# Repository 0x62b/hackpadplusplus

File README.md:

# Hackpad++
6-key hot-swappable RGB backlit macropad based on Seeed Studio Xiao NRF52840. Uses ZMK for firmware.
400mAh battery, supports wireless BLE HID operation. I made this to use up some spare parts and learn more about ZMK.

Rn the firmware is in a really really really stripped down state because I want to get the physical thing before trying to make more firmware since it keeps breaking the build

According to ZMK's [power profiler](https://zmk.dev/power-profiler) we should get about 21 hours of battery life with the RGB at 20% brightness

## Repo Structure
CAD files in `cad/`\
KiCad design files in `PCB/`\
Production gerbers in `PCB/gerbers`\
Firmware in `firmware/`\
BOM at `bom.csv`\
Case Onshape design [here](https://cad.onshape.com/documents/916857c7e80611f775a72b60/w/b9c69dbfc296334dd1ffd629/e/9b910e13e67ad3b8cb3a877d?renderMode=0&uiState=69eb64186156e8d7dafdc7be)

## 3D Models
https://grabcad.com/library/oled-0-91-128x32-1
https://grabcad.com/library/seeed-studio-xiao-nrf52840-sense-1
https://grabcad.com/library/kailh-polia-switch-cherry-mx-compatible-1
https://grabcad.com/library/11mm-metal-shaft-rotary-encoders-tht-vertical-w-push-on-switch-1
https://grabcad.com/library/dsa-keycap-for-cherry-mx-switches-1

# Assembly
Prerequisites: solder the PCB and print the case
1. put switches into sockets
2. put PCB assembly into bottom case
3. put top case over the assembly
4. screw in the top case with M3 screws
5. attach keycaps to switches
6. flash firmware according to ZMK docs
7. yay

## Cost
BOM: 17.38 USD\
PCB: 4 USD + 1.5 USD shipping\
Total: 22.88 USD

|Item              |Unit Price (AUD)|Quantity|Extended Price (AUD)|Extended Price(USD)|Notes                                  |Link                                                                                                                             |
|------------------|----------------|--------|--------------------|-------------------|---------------------------------------|---------------------------------------------------------------------------------------------------------------------------------|
|Switches          |0               |6       |0                   |0                  |Owned                                  |https://www.aliexpress.com/item/1005007983672026.html                                                                            |
|Hotswap sockets   |0               |6       |0                   |0                  |Extra from keeb                        |https://www.aliexpress.com/item/1005007232040760.html                                                                            |
|Diodes            |0               |6       |0                   |0                  |Extra from keeb                        |https://www.aliexpress.com/item/1005006323468521.html                                                                            |
|LEDs              |0               |6       |0                   |0                  |Owned - link is example                |https://www.aliexpress.com/item/1005005193716172.html                                                                            |
|Xiao              |19.25           |1       |19.25               |13.77              |ITS CHEAPER THAN ALIEXPRESS IVE CHECKED|https://core-electronics.com.au/seeed-studio-xiao-nrf52840-pre-soldered-bluetooth-5-0-ble-wireless-iot-microcontroller-board.html|
|Keycaps           |0               |6       |0                   |0                  |Owned - link is example                |https://aliexpress.com/item/1005011909872629.html                                                                                |
|OLED              |0               |1       |0                   |0                  |Owned                                  |https://www.lcsc.com/product-detail/C5248081.html                                                                                |
|Battery           |5.05            |1       |5.05                |3.61               |N/A                                    |https://core-electronics.com.au/polymer-lithium-ion-battery-400mah-38456.html                                                    |
|M3 heatset inserts|0               |4       |0                   |0                  |owned                                  |N/A                                                                                                                              |
|M3x10 screws      |0               |4       |0                   |0                  |owned                                  |N/A                                                                                                                              |
|PCB               |N/A             |1       |N/A                 |6.5                |N/A                                    |https://jlcpcb.com                                                                                                               |

## Images
### Schematic

### PCB layout

### PCB render

### Full render

### Zine page

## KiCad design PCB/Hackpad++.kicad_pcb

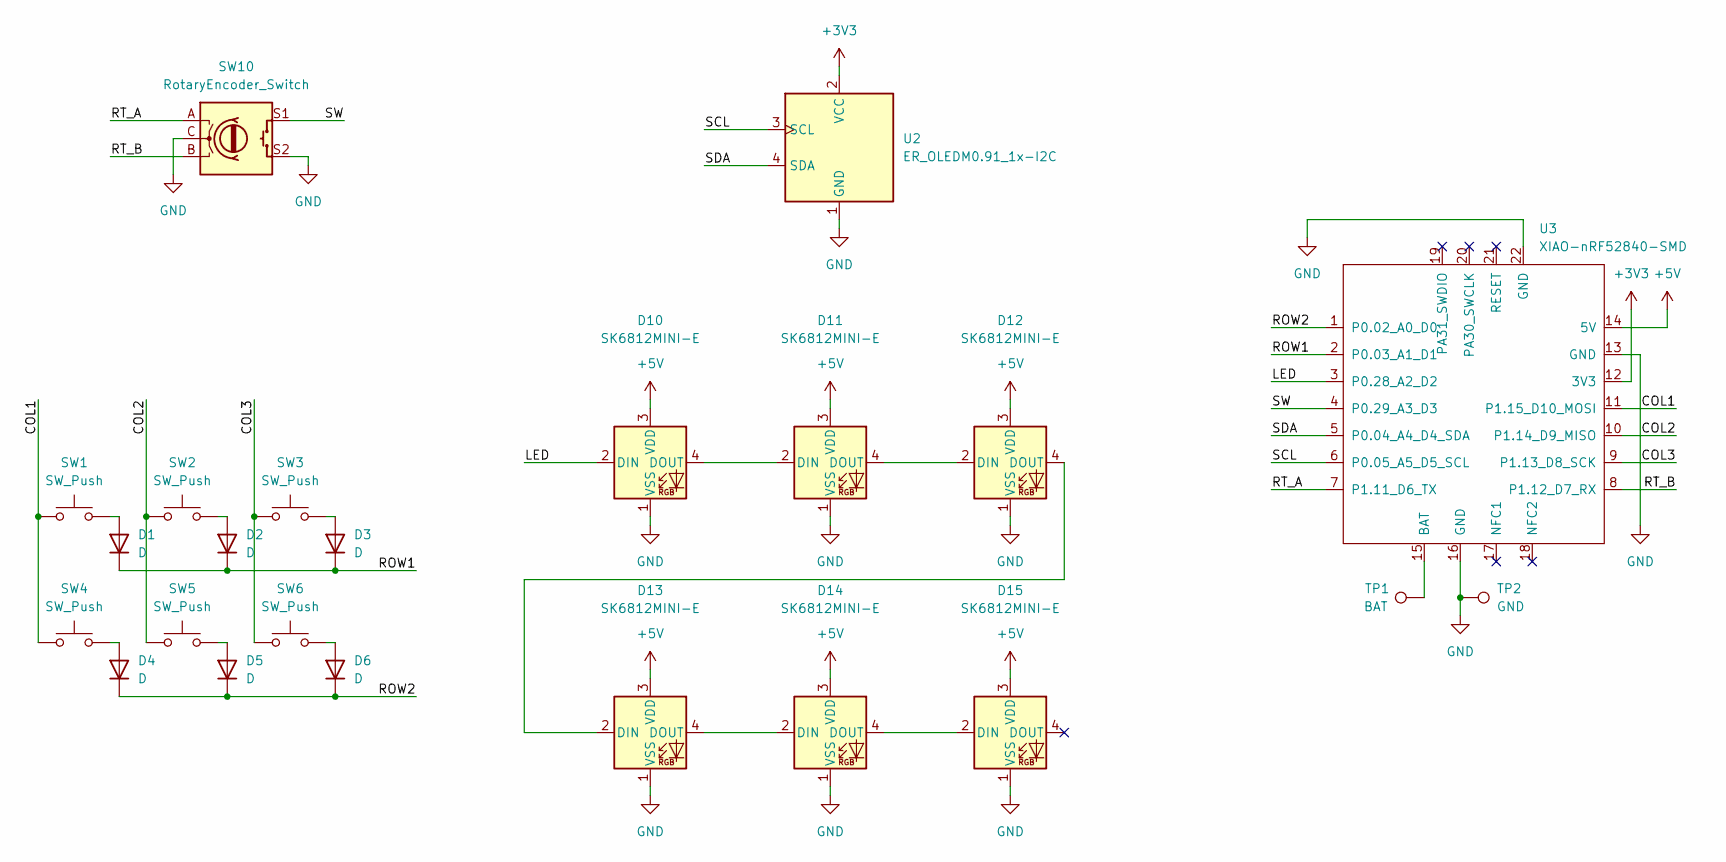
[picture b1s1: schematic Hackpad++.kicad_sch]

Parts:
D1, D2, D3, D4, D5, D6: D; D_SOD-123
D10, D11, D12, D13, D14, D15: SK6812MINI-E; LED_SK6812MINI-E_3.2x2.8mm_P1.5mm_ReverseMount
SW1, SW2, SW3, SW4, SW5, SW6: SW_Push; MX-Hotswap-1U
SW10: RotaryEncoder_Switch; RotaryEncoder_Alps_EC11E-Switch_Vertical_H20mm
TP1: BAT; TestPoint_Pad_2.0x2.0mm
TP2: GND; TestPoint_Pad_2.0x2.0mm
U2: ER_OLEDM0.91_1x-I2C
U3: XIAO-nRF52840-SMD

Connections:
+3V3: U2.2 (VCC), U3.12 (3V3)
+5V: D10.3 (VDD), D11.3 (VDD), D12.3 (VDD), D13.3 (VDD), D14.3 (VDD), D15.3 (VDD), U3.14 (5V)
/COL1: SW1.1, SW4.1, U3.11 (P1.15_D10_MOSI)
/COL2: SW2.1, SW5.1, U3.10 (P1.14_D9_MISO)
/COL3: SW3.1, SW6.1, U3.9 (P1.13_D8_SCK)
/LED: D10.2 (DIN), U3.3 (P0.28_A2_D2)
/ROW1: D1.1 (K), D2.1 (K), D3.1 (K), U3.2 (P0.03_A1_D1)
/ROW2: D4.1 (K), D5.1 (K), D6.1 (K), U3.1 (P0.02_A0_D0)
/RT_A: SW10.A, U3.7 (P1.11_D6_TX)
/RT_B: SW10.B, U3.8 (P1.12_D7_RX)
/SCL: U2.3 (SCL), U3.6 (P0.05_A5_D5_SCL)
/SDA: U2.4 (SDA), U3.5 (P0.04_A4_D4_SDA)
/SW: SW10.S1, U3.4 (P0.29_A3_D3)
GND: D10.1 (VSS), D11.1 (VSS), D12.1 (VSS), D13.1 (VSS), D14.1 (VSS), D15.1 (VSS), SW10.C, SW10.S2, TP2.1 (1_1), U2.1 (GND), U3.13 (GND), U3.16 (GND), U3.22 (GND)
unnamed: D1.2 (A), SW1.2
unnamed: D2.2 (A), SW2.2
unnamed: D3.2 (A), SW3.2
unnamed: D4.2 (A), SW4.2
unnamed: D5.2 (A), SW5.2
unnamed: D6.2 (A), SW6.2
unnamed: D10.4 (DOUT), D11.2 (DIN)
unnamed: D11.4 (DOUT), D12.2 (DIN)
unnamed: D12.4 (DOUT), D13.2 (DIN)
unnamed: D13.4 (DOUT), D14.2 (DIN)
unnamed: D14.4 (DOUT), D15.2 (DIN)
unnamed: TP1.1 (1_1), U3.15 (BAT)

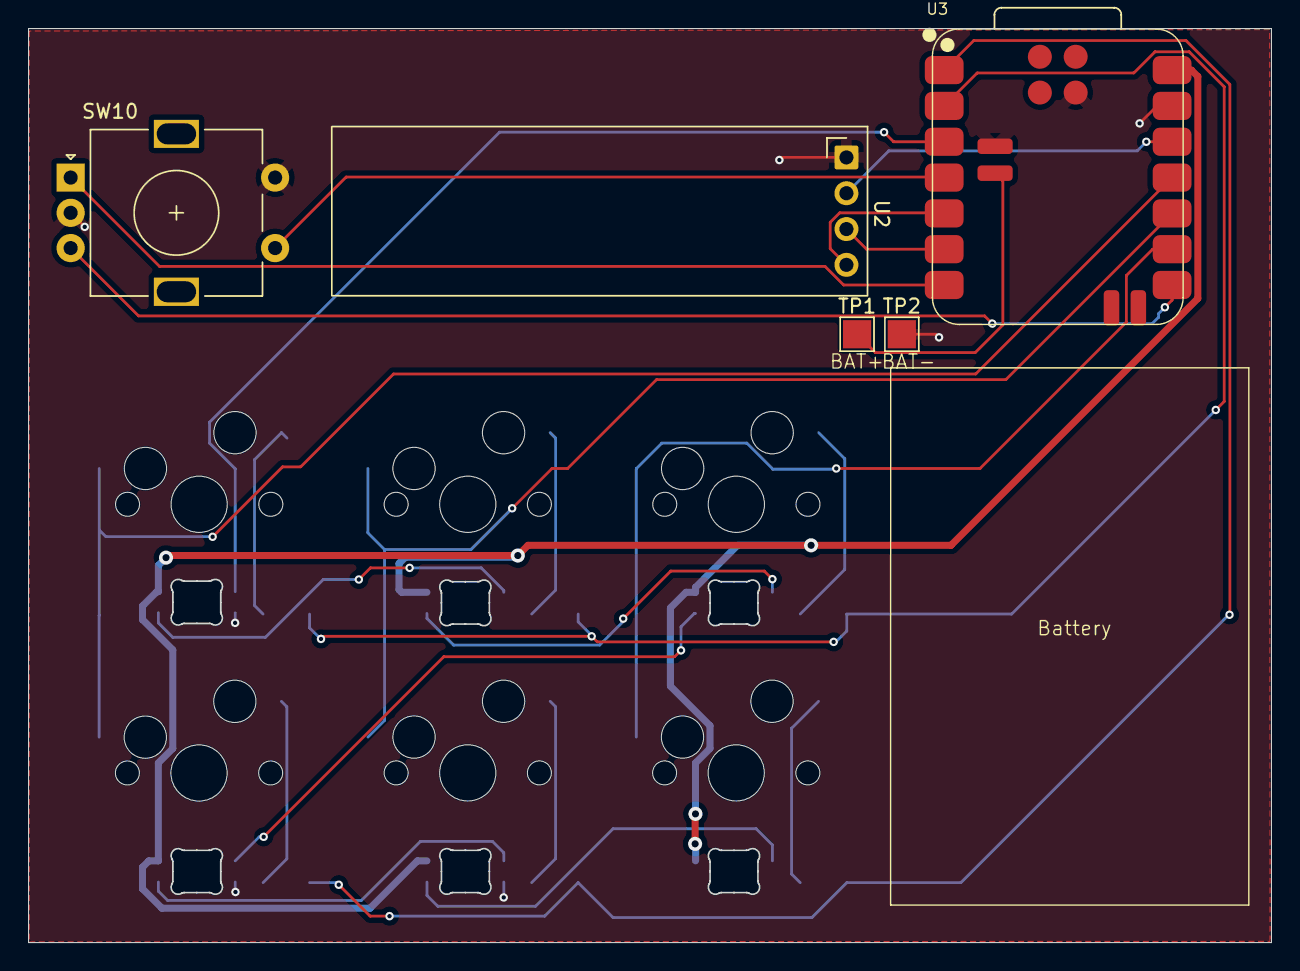
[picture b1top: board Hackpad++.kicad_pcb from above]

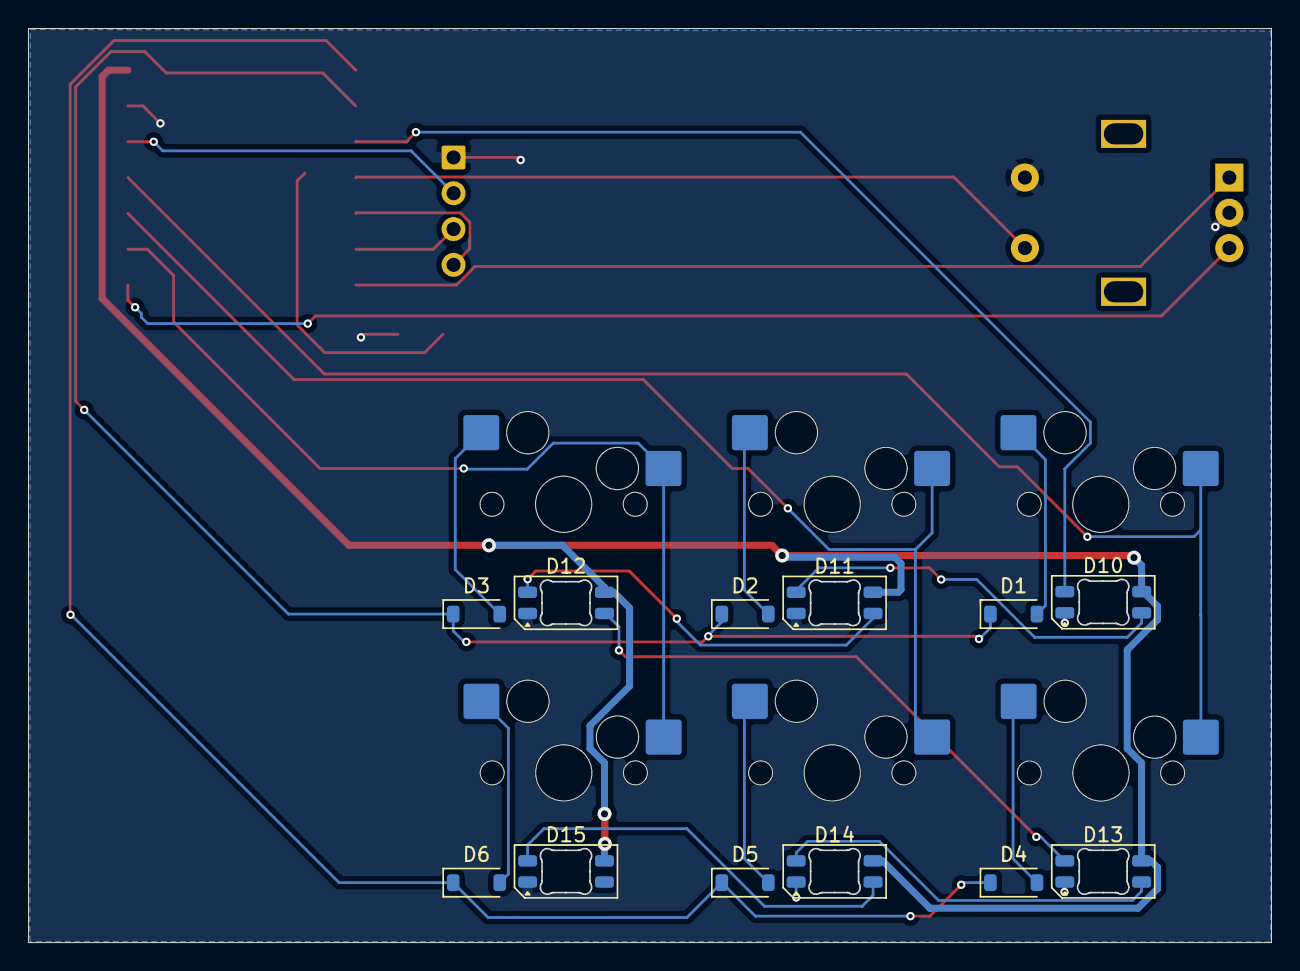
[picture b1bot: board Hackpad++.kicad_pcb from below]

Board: 2 copper layers, 88.1 x 64.8 mm, 23 parts (18 on the bottom side), 26 nets.

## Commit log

2026-04-24 add case and plate cad files
2026-04-24 add onshape link
2026-04-24 add full assembly step
2026-04-24 add full assembly render image
2026-04-24 add links to bom
2026-04-24 add cost
2026-04-24 fix cost
2026-04-25 zine page
2026-04-25 add firmware submodule
2026-04-29 add assembly instructions
    people who needed this are the people who need instructions on a shampoo bottle
2026-05-01 new zine
2026-05-01 newer zine
